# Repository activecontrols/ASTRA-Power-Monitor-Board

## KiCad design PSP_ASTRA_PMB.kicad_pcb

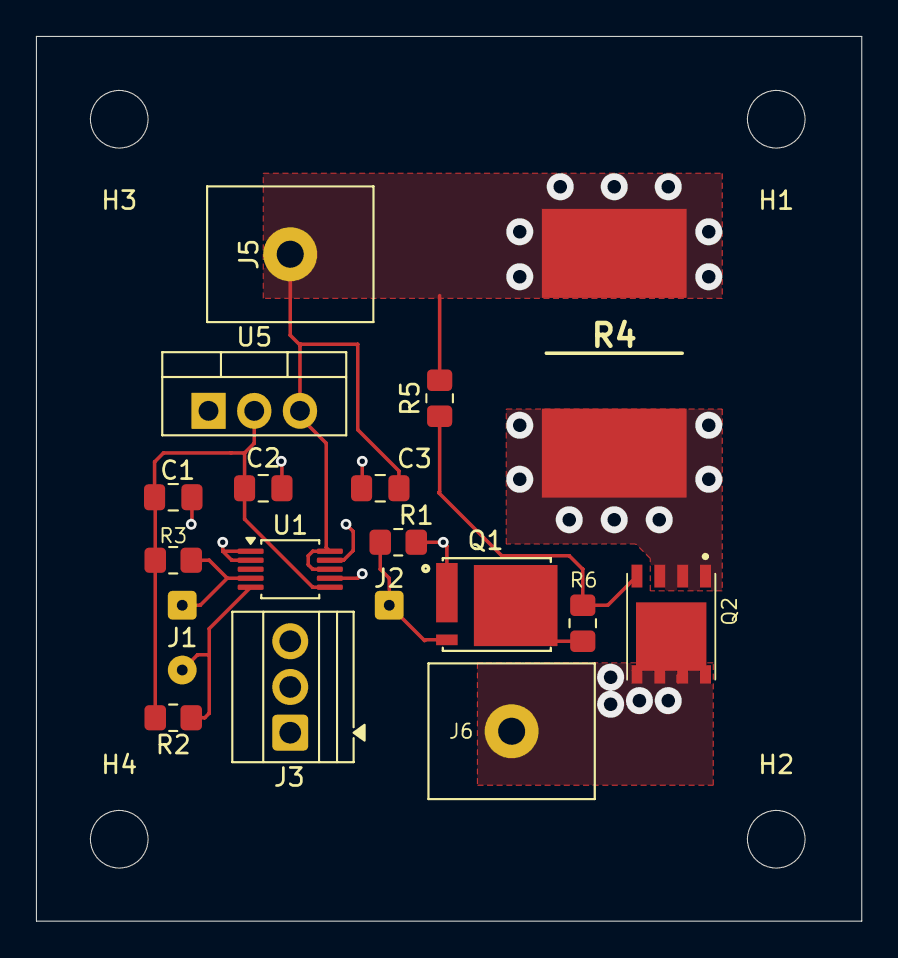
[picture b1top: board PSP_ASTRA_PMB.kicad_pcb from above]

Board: 4 copper layers, 45.8 x 49.1 mm, 22 parts (0 on the bottom side), 10 nets.

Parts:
C1, C3: 0.1 u; C_0805_2012Metric_Pad1.18x1.45mm_HandSolder
C2: 10u; C_0805_2012Metric_Pad1.18x1.45mm_HandSolder
H1, H2, H3, H4: MountingHole; MountingHole_3.2mm_M3
J1: Conn_01x02_Socket; SolderWire-0.1sqmm_1x02_P3.6mm_D0.4mm_OD1mm
J2: Conn_01x01_Socket; SolderWire-0.1sqmm_1x01_D0.4mm_OD1mm
J3: Screw_Terminal_01x03; TerminalBlock_Xinya_XY308-2.54-3P_1x03_P2.54mm_Horizontal
J5, J6: Screw_Terminal_01x01; TerminalBlock_MetzConnect_360271_1x01_Horizontal_ScrewM3.0_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
Q1: BSC014N04LSIATMA1; MOSFETPMB
Q2: PMOS; PMOSPMB
R1, R5: 10k; R_0805_2012Metric_Pad1.20x1.40mm_HandSolder
R2, R3: 4.7k; R_0805_2012Metric_Pad1.20x1.40mm_HandSolder
R4: 0.5m; ShuntResistorPMB
R6: 10; R_0805_2012Metric_Pad1.20x1.40mm_HandSolder
U1: INA226; VSSOP-10_3x3mm_P0.5mm
U5: LD1117V33; TO-220-3_Vertical

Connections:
+12V: C3.1, J5.1, R4.1, R5.2, U1.8 (Vbus), U1.10 (Vin+), U5.3 (VI)
/Microcontroller: J2.1, Q1.4, R1.1
/NMOS Drain: Q1.8, R6.1
/PMOS Drain: J6.1, Q2.5, Q2.6, Q2.7, Q2.8, Q2.9, Q2.10, Q2.11
/PMOS Gate: Q2.4, R5.1, R6.2
/PMOS Source: Q2.1 (D), Q2.2 (G), Q2.3 (S), R4.2, U1.9 (Vin-)
GND: C1.1, C2.2, C3.2, J3.1, J3.2, J3.3, Q1.1 (D), R1.2, U1.1 (A1), U1.2 (A0), U1.7 (GND), U5.1 (GND)
unnamed: J1.1, R3.2, U1.4 (SDA)
unnamed: J1.2, R2.2, U1.5 (SCL)
unnamed: C1.2, C2.1, R2.1, R3.1, U1.6 (VS), U5.2 (VO)

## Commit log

2025-09-27 Add files via upload
    astra pmb schematic v1
2025-10-17 Add files via upload
    shunt resistor footprint added
2025-10-18 remove old sch
2025-11-01 Create Footprints
2025-11-01 Create placeholder
2025-11-01 Add files via upload
    added pmos and voltage divider (see schematic)
